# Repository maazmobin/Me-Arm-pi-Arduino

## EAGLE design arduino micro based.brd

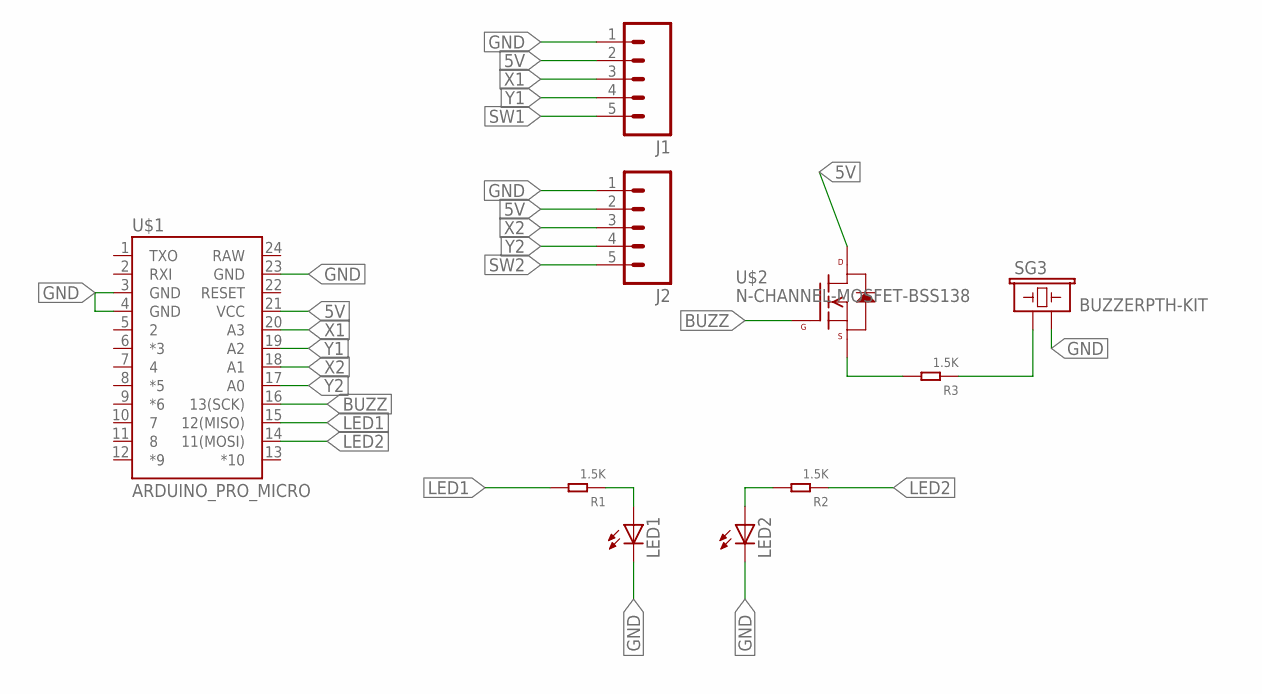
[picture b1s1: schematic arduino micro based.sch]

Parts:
J1, J2: M05JST-VERT; JST-5-PTH-VERT
LED1, LED2: LED5MM
R1, R2, R3: 1.5K; R0603
SG3: BUZZERPTH-KIT; BUZZER-12MM-KIT
U$1: ARDUINO_PRO_MICRO
U$2: N-CHANNEL-MOSFET-BSS138; SOT23-3

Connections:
5V: J1.2, J2.2, U$1.21 (VCC), U$2.3 (D)
BUZZ: U$1.16 (13(SCK)), U$2.1 (G)
GND: J1.1, J2.1, LED1.K (C), LED2.K (C), SG3.- (2), U$1.3 (GND), U$1.4 (GND), U$1.23 (GND)
LED1: R1.2, U$1.15 (12(MISO))
LED2: R2.1, U$1.14 (11(MOSI))
unnamed: LED1.A, R1.1
unnamed: LED2.A, R2.2
unnamed: R3.1, SG3.+ (1)
unnamed: R3.2, U$2.2 (S)
SW1: J1.5
SW2: J2.5
X1: J1.3, U$1.20 (A3)
X2: J2.3, U$1.18 (A1)
Y1: J1.4, U$1.19 (A2)
Y2: J2.4, U$1.17 (A0)

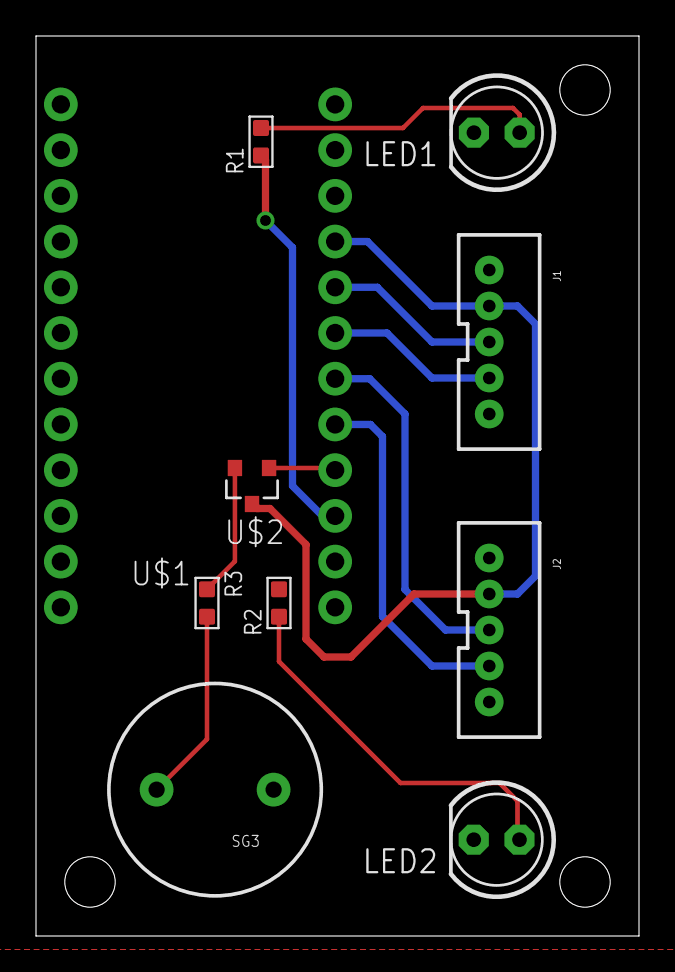
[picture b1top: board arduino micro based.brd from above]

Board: 2 copper layers, 33.5 x 50.0 mm, 10 parts (0 on the bottom side), 13 nets.

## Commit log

2017-06-01 :confetti_ball: Added .gitattributes & .gitignore files
2017-06-01 layout completed
2017-06-03 me arm pi, layout completed
2017-06-03 schematic edit

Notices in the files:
parts and their libraries:
SparkFun-Connectors: Licensing: Creative Commons ShareAlike 4.0 International - https://creativecommons.org/licenses/by-sa/4.0
